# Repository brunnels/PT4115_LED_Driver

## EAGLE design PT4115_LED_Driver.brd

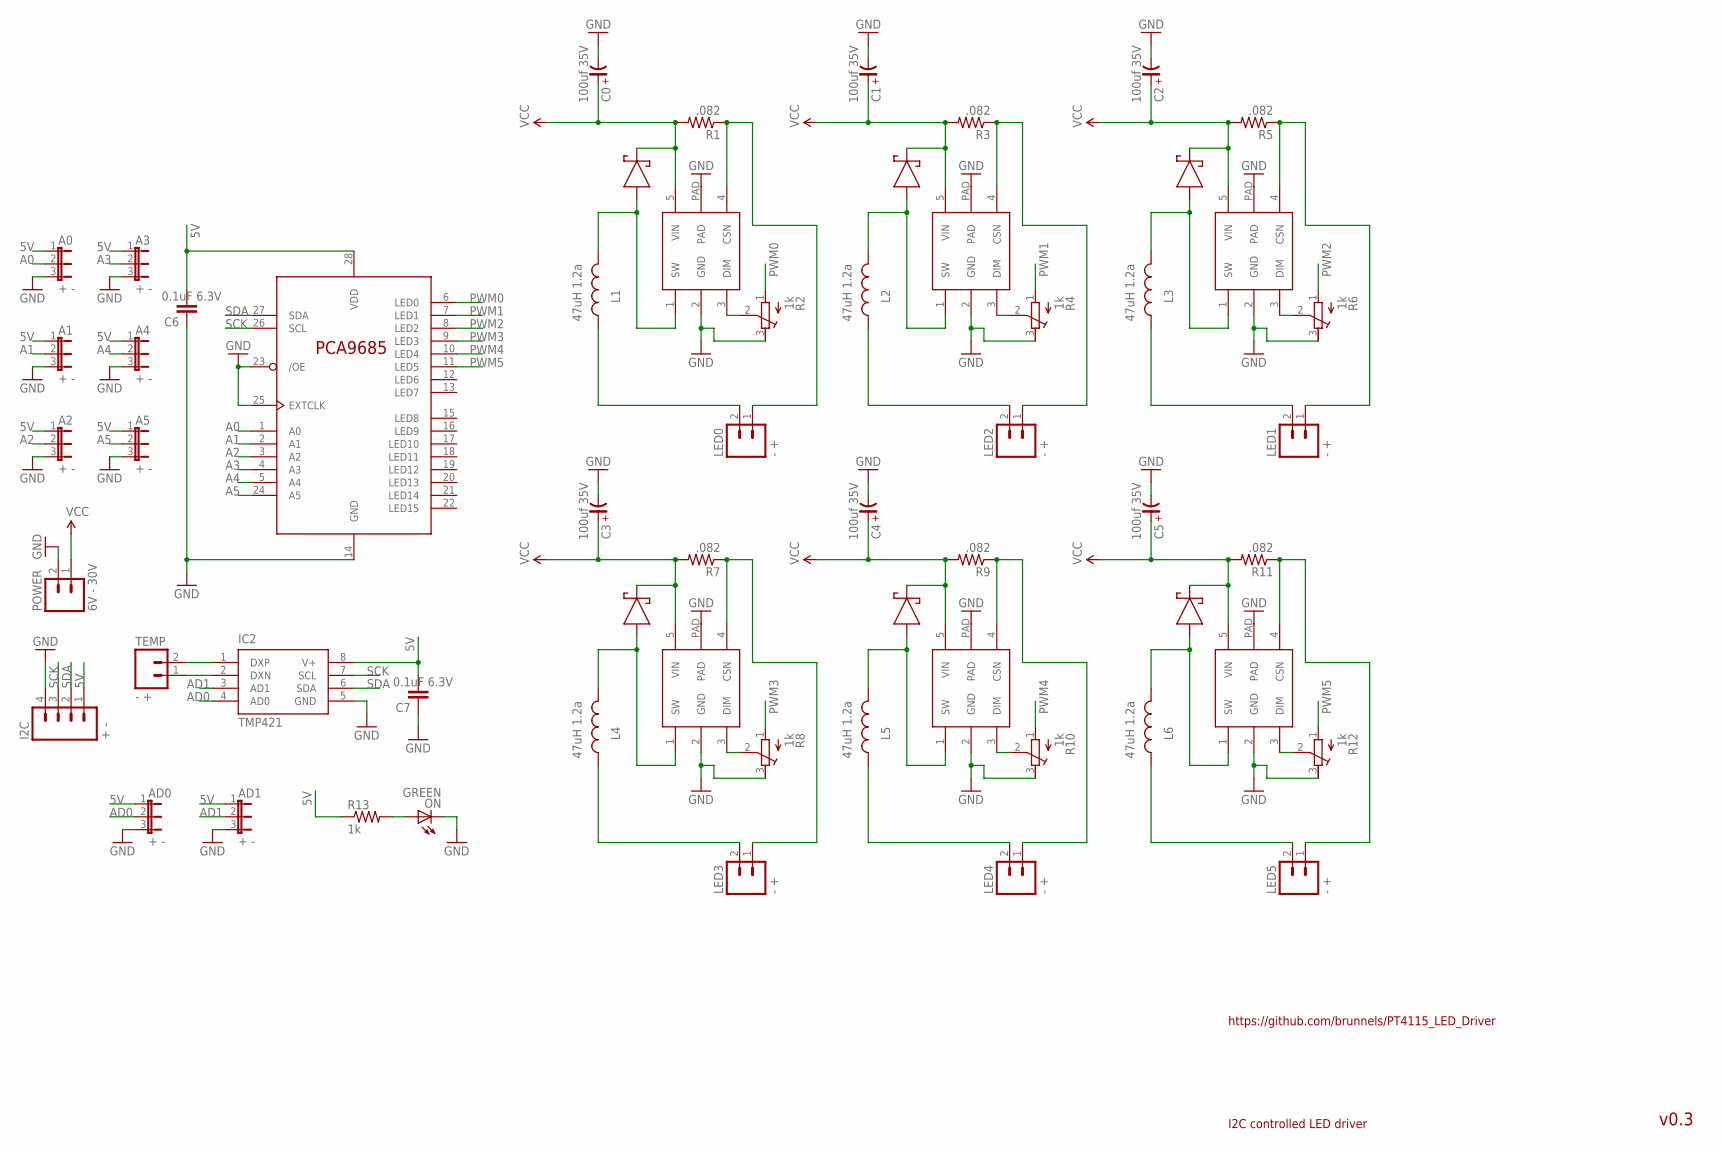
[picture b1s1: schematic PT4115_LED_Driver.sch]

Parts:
A0, A1, A2, A3, A4, A5: + -; SJ_3
AD0, AD1: + -; SJ_3
C0, C1, C2, C3, C4, C5: 100uf 35V; CSV-E/F
C6, C7: 0.1uF 6.3V; 0805
D1, D2, D3, D4, D5, D6: SCHOTTKY_DIODE-SS18; DO-214
DRV0, DRV1, DRV2, DRV3, DRV4, DRV5: PT4115; SOT89-5
I2C: + -; MOLEX-1X4
IC1: PCA9685PW; TSSOP28
IC2: TMP421; SOT23-8
L1, L2, L3, L4, L5, L6: 47uH 1.2a; CR54
LED0, LED1, LED2, LED3, LED4, LED5: - +; SCREWTERMINAL-3.5MM-2
ON: GREEN; CHIPLED_0805
POWER: 6V - 30V; SCREWTERMINAL-3.5MM-2
R1, R3, R5, R7, R9, R11: .082; 1206
R2, R4, R6, R8, R10, R12: 1k; RTRIM3296W
R13: 1k; 0603-RES
TEMP: - +; 1X02

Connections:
5V: A0.1, A1.1, A2.1, A3.1, A4.1, A5.1, AD0.1, AD1.1, C6.2, C7.2, I2C.1, IC1.28 (VDD), IC2.8 (V+), R13.1
A0: A0.2, IC1.1 (A0)
A1: A1.2, IC1.2 (A1)
A2: A2.2, IC1.3 (A2)
A3: A3.2, IC1.4 (A3)
A4: A4.2, IC1.5 (A4)
A5: A5.2, IC1.24 (A5)
AD0: AD0.2, IC2.4 (AD0)
AD1: AD1.2, IC2.3 (AD1)
GND: A0.3, A1.3, A2.3, A3.3, A4.3, A5.3, AD0.3, AD1.3, C0.-, C1.-, C2.-, C3.-, C4.-, C5.-, C6.1, C7.1, DRV0.2 (GND), DRV0.PAD, DRV1.2 (GND), DRV1.PAD, DRV2.2 (GND), DRV2.PAD, DRV3.2 (GND), DRV3.PAD, DRV4.2 (GND), DRV4.PAD, DRV5.2 (GND), DRV5.PAD, I2C.4, IC1.14 (GND), IC1.23 (/OE), IC1.25 (EXTCLK), IC2.5 (GND), ON.C, POWER.2, R2.3 (A), R4.3 (A), R6.3 (A), R8.3 (A), R10.3 (A), R12.3 (A)
unnamed: DRV1.4 (CSN), LED2.1, R3.1
unnamed: IC2.1 (DXP), TEMP.2
unnamed: IC2.2 (DXN), TEMP.1
unnamed: D1.P$2 (ANODE), DRV1.1 (SW), L2.P$2 (2)
unnamed: DRV1.3 (DIM), R4.2 (S)
unnamed: DRV0.4 (CSN), LED0.1, R1.1
unnamed: D3.P$2 (ANODE), DRV0.1 (SW), L1.P$2 (2)
unnamed: DRV0.3 (DIM), R2.2 (S)
unnamed: L1.P$1 (1), LED0.2
unnamed: L2.P$1 (1), LED2.2
unnamed: DRV2.4 (CSN), LED1.1, R5.1
unnamed: D2.P$2 (ANODE), DRV2.1 (SW), L3.P$2 (2)
unnamed: DRV2.3 (DIM), R6.2 (S)
unnamed: L3.P$1 (1), LED1.2
unnamed: DRV3.4 (CSN), LED3.1, R7.1
unnamed: D4.P$2 (ANODE), DRV3.1 (SW), L4.P$2 (2)
unnamed: DRV3.3 (DIM), R8.2 (S)
unnamed: L4.P$1 (1), LED3.2
unnamed: DRV4.4 (CSN), LED4.1, R9.1
unnamed: D5.P$2 (ANODE), DRV4.1 (SW), L5.P$2 (2)
unnamed: DRV4.3 (DIM), R10.2 (S)
unnamed: L5.P$1 (1), LED4.2
unnamed: DRV5.4 (CSN), LED5.1, R11.1
unnamed: D6.P$2 (ANODE), DRV5.1 (SW), L6.P$2 (2)
unnamed: DRV5.3 (DIM), R12.2 (S)
unnamed: L6.P$1 (1), LED5.2
unnamed: ON.A, R13.2
PWM0: IC1.6 (LED0), R2.1 (E)
PWM1: IC1.7 (LED1), R4.1 (E)
PWM2: IC1.8 (LED2), R6.1 (E)
PWM3: IC1.9 (LED3), R8.1 (E)
PWM4: IC1.10 (LED4), R10.1 (E)
PWM5: IC1.11 (LED5), R12.1 (E)
SCK: I2C.3, IC1.26 (SCL), IC2.7 (SCL)
SDA: I2C.2, IC1.27 (SDA), IC2.6 (SDA)
VCC: C0.+, C1.+, C2.+, C3.+, C4.+, C5.+, D1.P$1 (CATHODE), D2.P$1 (CATHODE), D3.P$1 (CATHODE), D4.P$1 (CATHODE), D5.P$1 (CATHODE), D6.P$1 (CATHODE), DRV0.5 (VIN), DRV1.5 (VIN), DRV2.5 (VIN), DRV3.5 (VIN), DRV4.5 (VIN), DRV5.5 (VIN), POWER.1, R1.2, R3.2, R5.2, R7.2, R9.2, R11.2

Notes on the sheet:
v0.3
I2C controlled LED driver
https://github.com/brunnels/PT4115_LED_Driver

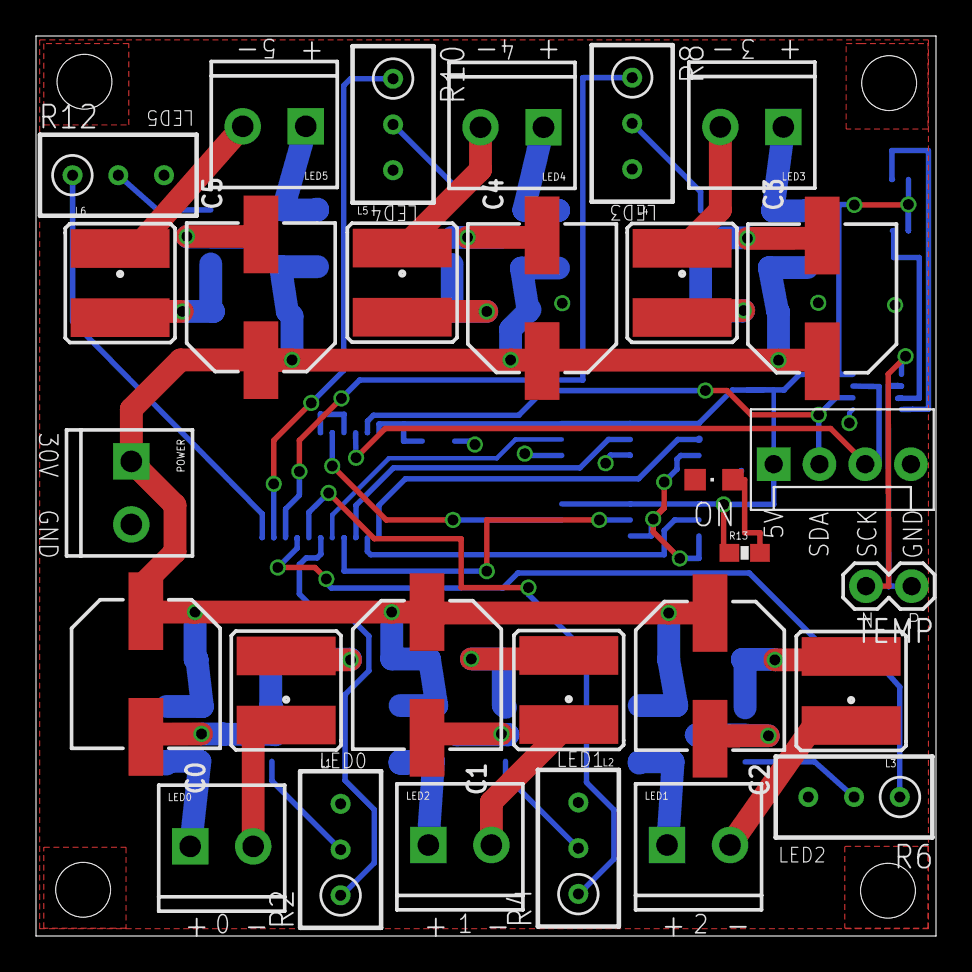
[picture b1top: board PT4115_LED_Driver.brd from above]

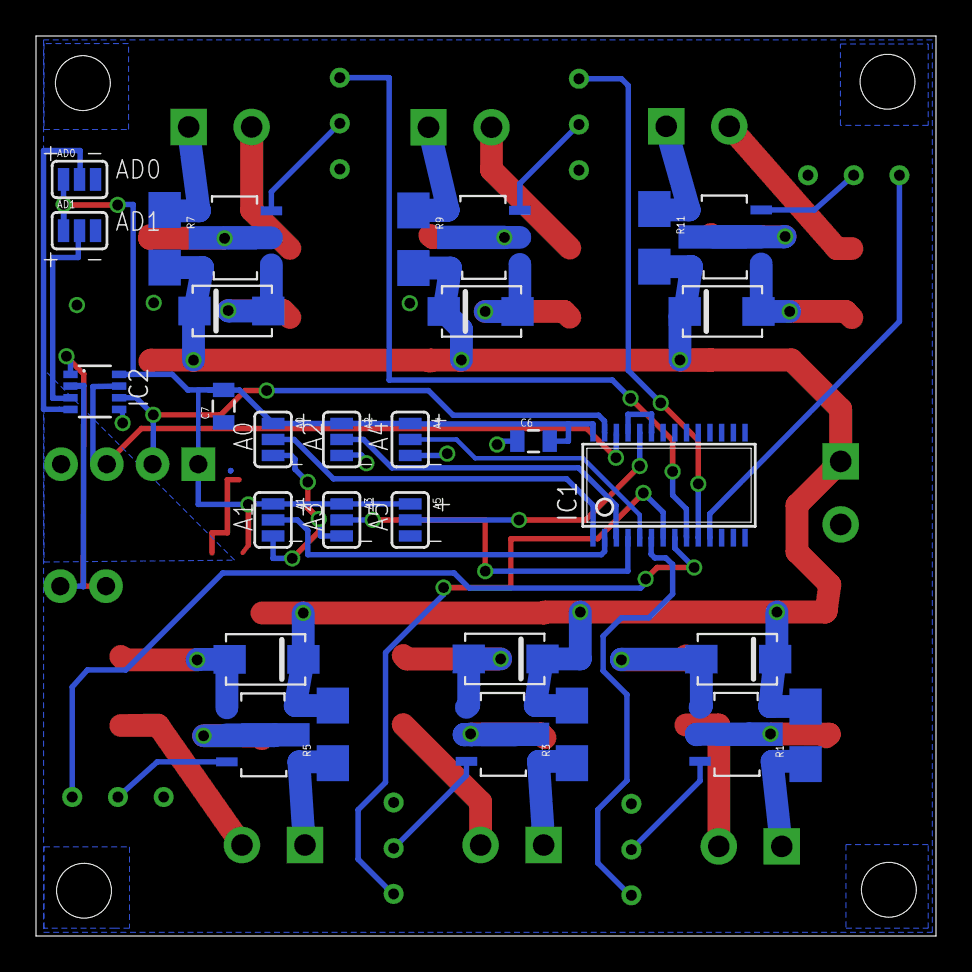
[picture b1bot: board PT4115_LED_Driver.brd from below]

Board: 2 copper layers, 50.0 x 50.0 mm, 63 parts (30 on the bottom side), 46 nets.

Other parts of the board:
5V, 5V1: STAND-OFF-TIGHT
U$3, U$4: STAND-OFF-TIGHT

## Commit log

2012-03-04 Creating repo
2012-03-04 Initial checkin
2012-03-04 Simplified some routes. Cleaned up ground and 5v planes. Added img exports.
2012-03-04 Added led 5v power indicator
2012-03-05 Switched to larger Panasinonic F size capacitors for low ESR part availability.
2012-03-05 Switched to larger pad for inductor to source 1.2a part. Switched top plane from 5V to GND.
2012-04-18 Fixed issues with ground pad on TMP421 address jumper. Moved mounting holes to provide better clearance. Fixed silkscreen labeling problems with PCA9685 jumper and TMP421 external temp jumper.

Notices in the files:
parts and their libraries:
SparkFun: Licensing: CC v3.0 Share-Alike You are welcome to use this library for commercial purposes.
rc-master: Copyright (C) 2007, Bob Starr
